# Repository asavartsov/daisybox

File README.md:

# daisybox

Box with daisy seed and IO

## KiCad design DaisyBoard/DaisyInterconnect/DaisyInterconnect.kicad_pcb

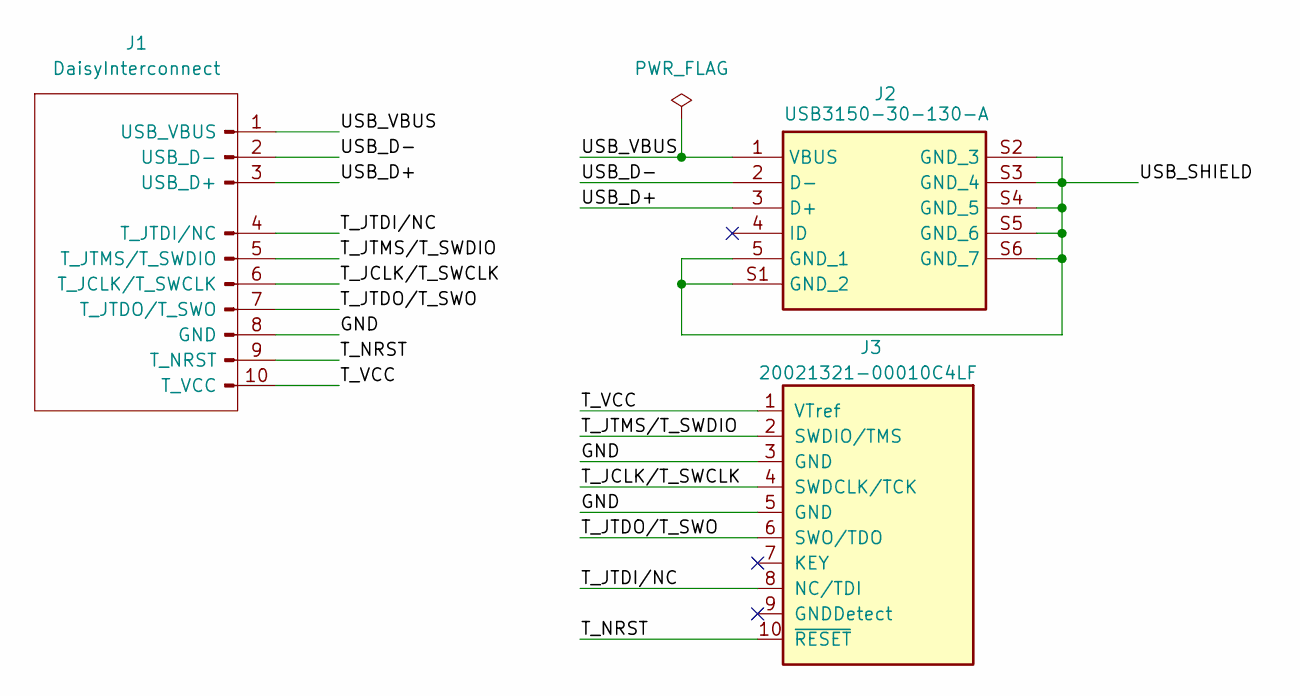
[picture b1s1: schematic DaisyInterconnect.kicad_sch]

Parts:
J1: DaisyInterconnect
J2: USB3150-30-130-A; USB315030130A; Manufacturer_Part_Number USB3150-30-130-A
J3: 20021321-00010C4LF; 2x05_P1.27mm; MPN 20021321-00010C4LF

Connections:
/GND: J1.8 (GND), J3.3 (GND), J3.5 (GND)
/T_JCLK/T_SWCLK: J1.6 (T_JCLK/T_SWCLK), J3.4 (SWDCLK/TCK)
/T_JTDI/NC: J1.4 (T_JTDI/NC), J3.8 (NC/TDI)
/T_JTDO/T_SWO: J1.7 (T_JTDO/T_SWO), J3.6 (SWO/TDO)
/T_JTMS/T_SWDIO: J1.5 (T_JTMS/T_SWDIO), J3.2 (SWDIO/TMS)
/T_NRST: J1.9 (T_NRST), J3.10 (~RESET)
/T_VCC: J1.10 (T_VCC), J3.1 (VTref)
/USB_D+: J1.3 (USB_D+), J2.3 (D+)
/USB_D-: J1.2 (USB_D-), J2.2 (D-)
/USB_SHIELD: J2.5 (GND_1), J2.S1 (GND_2), J2.S2 (GND_3), J2.S3 (GND_4), J2.S4 (GND_5), J2.S5 (GND_6), J2.S6 (GND_7)
/USB_VBUS: J1.1 (USB_VBUS), J2.1 (VBUS)

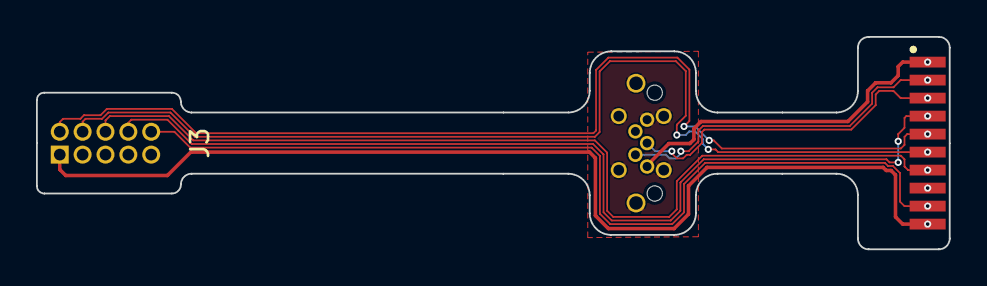
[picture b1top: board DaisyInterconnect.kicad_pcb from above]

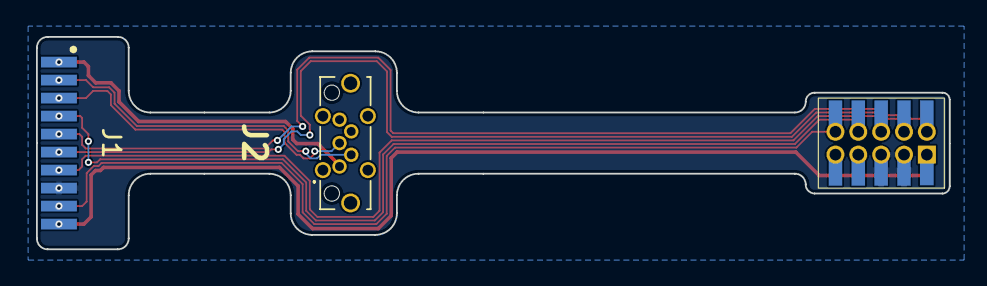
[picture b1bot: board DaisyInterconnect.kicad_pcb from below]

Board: 2 copper layers, 50.7 x 11.8 mm, 3 parts (2 on the bottom side), 11 nets.

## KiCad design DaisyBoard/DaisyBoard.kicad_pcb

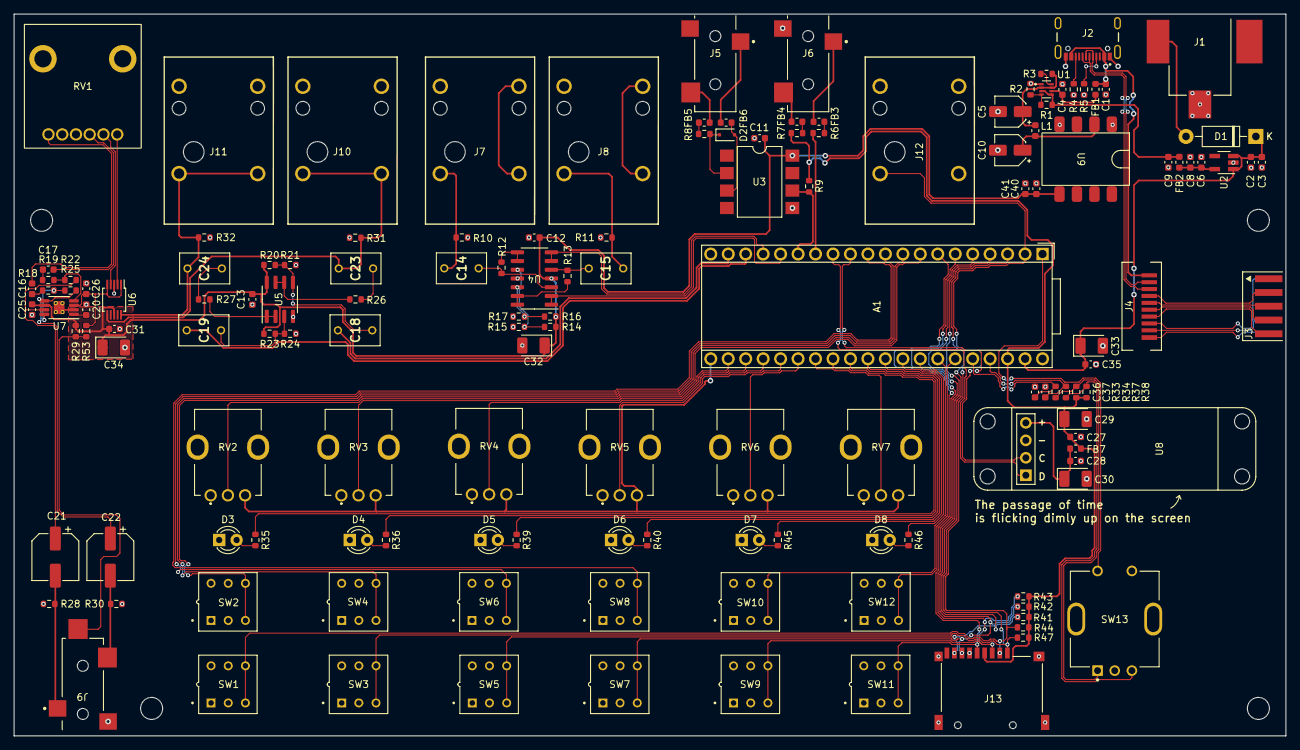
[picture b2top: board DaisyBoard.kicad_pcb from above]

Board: 2 copper layers, 185.0 x 105.0 mm, 149 parts (0 on the bottom side), 111 nets.

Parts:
A1: Electrosmith_Daisy_Seed_Rev4; Electrosmith_Daisy_Seed
C1, C3, C8, C27, C35, C36, C37: 10n; C_0603_1608Metric
C2, C4, C6, C9, C40, C41: 4.7uF; C_0603_1608Metric
C5, C10: 4.7uF; CP_Elec_4x5.4
C11, C12, C13, C20, C25, C26, C28, C31: 100n; C_0603_1608Metric
C14, C15, C18, C19, C23, C24: 1uF; B32529C0105J189
C16, C17: 470n; C_0603_1608Metric
C21, C22: 220uF; CP_Elec_6.3x5.7
C29, C30, C32, C33, C34: 10uF; CP_EIA-3528-15_AVX-H_Pad1.50x2.35mm_HandSolder
D1: 1N5817-T; D_DO-41_SOD81_P10.16mm_Horizontal
D2: 1N4148WS; D_SOD-323F
D3, D4, D5, D6, D7, D8: White; QBL7IW60D-NW
FB1, FB2, FB7: 33 Ohm @ 100 MHz; L_0603_1608Metric
FB3, FB4, FB5, FB6: 1 kOhm @ 100 MHz; L_0603_1608Metric
H1, H2, H3, H4: MountingHole; MountingHole_3.2mm_M3
J1: RASM722X-ND; RASM722X
J2: USB4105-GF-A-120; GCT_USB4105GFA
J3: SWD/JTAG BTB; 009159010061916
J4: DaisyInterconnect
J5, J6: 35RASMT2BHNTRX
J7, J8, J10, J11, J12: ACJM-HHOP
J9: 35RASMT3BHNTRX
J13: 112J-TDAR-R01
L1: 6.8uH; L_0603_1608Metric
R1: 16k; R_0603_1608Metric
R2, R4, R5, R33, R34: 5k1; R_0603_1608Metric
R3, R28, R30, R37, R38: 10k; R_0603_1608Metric
R6: 10R; R_0603_1608Metric
R7: 33R; R_0603_1608Metric
R8: 220R; R_0603_1608Metric
R9: 270R; R_0603_1608Metric
R10, R11, R12, R13, R20, R21, R23, R24, R31, R32: 2M; R_0603_1608Metric
R14, R15, R16, R17: 100k; R_0603_1608Metric
R18, R19: 22k; R_0603_1608Metric
R22, R25, R53: 33k; R_0603_1608Metric
R26, R27: 100R; R_0603_1608Metric
R29: 200k; R_0603_1608Metric
R35, R36, R39, R40, R45, R46: 1k; R_0603_1608Metric
R41, R42, R43, R44, R47: 47k; R_0603_1608Metric
RV1: A50K; PTV112-4420A-A503
RV2, RV3, RV4, RV5, RV6, RV7: B10K; PTV09A-4025F-B103
SW1, SW3, SW5, SW7, SW9, SW11: TL2201OAZA; SW_TL2201EEZA
SW2, SW4, SW6, SW8, SW10, SW12: TL2201EEZA; SW_TL2201EEZA
SW13: PEC11H-4120F-S0020
U1: TPS2116DRLR; SOTFL50P160X60-8N
U2: LDK320AM50R; SOT-23-5_HandSoldering
U3: 6N138S; SMDIP-8_W9.53mm
U4: MCP6004T-I/SL; SOIC-14_3.9x8.7mm_P1.27mm
U5: MCP6002T-I/SN; SOIC-8_3.9x4.9mm_P1.27mm
U6: RS2102XN; MSOP-10_3x3mm_P0.5mm
U7: TPA6110A2DGN
U8: DFR0647
U9: IFS0105S05

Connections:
+3.3V: A1.38 (3V3_D), C27.1, C29.1, FB7.1, J13.4 (VDD), R7.2, R9.1, R37.1, R38.1, R41.1, R42.1, R43.1, R44.1, R47.1
+3.3VA: A1.21 (3V3_A), RV2.3, RV3.3, RV4.3, RV5.3, RV6.3, RV7.3
+3.3V_OLED: C28.1, C30.1, FB7.2, U8.4 (VCC)
+5V: C11.1, C12.1, C13.1, C25.1, C31.1, C32.1, C34.1, C40.1, C41.1, R14.1, R16.1, R20.1, R23.1, R29.1, U3.8 (VCC), U4.4 (V+), U5.8 (V+), U6.8 (VDD), U7.6 (VDD), U9.5 (+Vout)
+5V_DC: C9.1, FB2.2, R1.2, U1.3 (VIN1), U1.5 (MODE)
+5V_USB: C4.1, FB1.2, U1.6 (VIN2)
+9V: A1.39 (VIN), C2.1, C3.1, C33.1, C35.1, D1.1 (K), U2.1 (IN), U2.3 (EN)
/AnalogIO/HP_OUT_L: C21.2, J9.T, R28.1
/AnalogIO/HP_OUT_R: C22.2, J9.R, R30.1
/AnalogIO/L_IN_BIAS: R12.1, U4.8, U4.9 (-)
/AnalogIO/R_IN_BIAS: R13.1, U4.13 (-), U4.14
/DigitalIO/MIDI_IN_D1: FB5.1, J5.R
/DigitalIO/MIDI_IN_D2: FB6.1, J5.T
/DigitalIO/MIDI_OUT_D1: FB3.1, J6.T
/DigitalIO/MIDI_OUT_D2: FB4.1, J6.R
/Power/+5VMUX_LC_OUT: C10.1, L1.2, U9.2 (+Vin)
/Power/+5VMUX_OUT: C5.1, L1.1, R3.2, U1.2 (VOUT), U1.7 (VOUT)
/Power/+5V_DC_LDO: C6.1, C8.1, FB2.1, U2.5 (OUT)
/Power/+9V_DC_IN: D1.2 (A), J1.SLEEVE
AUDIO_L_IN: A1.16 (AUDIO_IN_1), U4.1, U4.2 (-)
AUDIO_L_OUT: A1.18 (AUDIO_OUT_1), C19.1
AUDIO_R_IN: A1.17 (AUDIO_IN_2), U4.6 (-), U4.7
AUDIO_R_OUT: A1.19 (AUDIO_OUT_2), C18.1
ENC_A: A1.36 (USB_D_-), C36.1, R33.2
ENC_B: A1.37 (USB_D_+), C37.1, R34.2
ENC_CLICK: A1.1 (USB_ID), SW13.S1
GND: A1.20 (AGND), A1.40 (DGND), C1.2, C2.2, C3.2, C4.2, C5.2, C6.2, C8.2, C9.2, C10.2, C11.2, C12.2, C13.2, C20.2, C25.2, C26.1, C27.2, C28.2, C29.2, C30.2, C31.2, C32.2, C33.2, C34.2, C35.2, C36.2, C37.2, C40.2, C41.2, D3.1 (K), D4.1 (K), D5.1 (K), D6.1 (K), D7.1 (K), D8.1 (K), J1.TIP, J2.A1_B12 (GND), J2.B1_A12 (GND), J6.S, J7.S, J8.S, J9.S, J10.S, J10.SN, J11.S, J11.SN, J12.S, J13.6 (VSS), J13.10 (SHIELD), R2.1, R4.1, R5.1, R10.2, R11.2, R15.2, R17.2, R21.2, R24.2, R28.2, R30.2, R31.2, R32.2, RV1.1, RV1.1*, RV2.1, RV3.1, RV4.1, RV5.1, RV6.1, RV7.1, SW1.2 (B), SW1.5 (B), SW2.2 (B), SW2.5 (B), SW3.2 (B), SW3.5 (B), SW4.2 (B), SW4.5 (B), SW5.2 (B), SW5.5 (B), SW6.2 (B), SW6.5 (B), SW7.2 (B), SW7.5 (B), SW8.2 (B), SW8.5 (B), SW9.2 (B), SW9.5 (B), SW10.2 (B), SW10.5 (B), SW11.2 (B), SW11.5 (B), SW12.2 (B), SW12.5 (B), SW13.C, SW13.S2, U1.1 (GND), U2.2 (GND), U3.5 (GND), U4.11 (V-), U5.4 (V-), U6.3 (GND), U7.2 (GND), U7.9 (GND), U8.3 (GND), U9.1 (-Vin), U9.4 (-Vout)
HP_DETECT: C26.2, R53.1, U6.1 (IN1), U6.5 (IN2), U7.3 (SHDN)
HP_VOL_L: RV1.3, U6.2 (S1B)
HP_VOL_R: RV1.3*, U6.4 (S2B)
LED_1: A1.28 (ADC_6), R35.2
LED_2: A1.29 (DAC_OUT2), R36.2
LED_3: A1.30 (DAC_OUT1), R39.2
LED_4: A1.31 (SAI2_MCLK), R40.2
LED_5: A1.32 (SAI2_SD_B), R45.2
LED_6: A1.33 (SAI2_SD_A), R46.2
MAIN_IN_L: C14.1, J7.T, R10.1
MAIN_IN_R: C15.1, J8.T, R11.1
MAIN_OUT_L: C24.2, J11.T, J11.TN, R32.1, U6.10 (D1)
MAIN_OUT_R: C23.2, J10.T, J10.TN, R31.1, U6.6 (D2)
MIDI_IN: A1.15 (USART1_RX), R9.2, U3.6 (VO2)
MIDI_OUT: A1.14 (USART1_TX), R6.2
unnamed: C16.1, RV1.2
unnamed: C16.2, R18.2
unnamed: C17.1, RV1.2*
unnamed: C17.2, R19.2
unnamed: C23.1, R26.2
unnamed: C24.1, R27.2
unnamed: D2.2 (A), FB6.2, U3.3 (C2)
unnamed: D2.1 (K), R8.2, U3.2 (C1)
unnamed: D3.2 (A), R35.1
unnamed: D4.2 (A), R36.1
unnamed: D5.2 (A), R39.1
unnamed: D6.2 (A), R40.1
unnamed: D7.2 (A), R45.1
unnamed: D8.2 (A), R46.1
unnamed: FB3.2, R6.1
unnamed: FB4.2, R7.1
unnamed: FB5.2, R8.1
unnamed: J2.A5 (CC1), R5.2
unnamed: J2.B5 (CC2), R4.2
unnamed: J3.6 (GND), J4.8 (GND)
unnamed: J3.4 (T_JCLK/T_SWCLK), J4.6 (T_JCLK/T_SWCLK)
unnamed: J3.2 (T_JTDI/NC), J4.4 (T_JTDI/NC)
unnamed: J3.5 (T_JTDO/T_SWO), J4.7 (T_JTDO/T_SWO)
unnamed: J3.3 (T_JTMS/T_SWDIO), J4.5 (T_JTMS/T_SWDIO)
unnamed: J3.9 (T_NRST), J4.9 (T_NRST)
unnamed: J3.10 (T_VCC), J4.10 (T_VCC)
unnamed: J7.SN, J7.TN
unnamed: J8.SN, J8.TN
unnamed: J9.TN, R29.2, R53.2
unnamed: R33.1, R37.2, SW13.A
unnamed: R34.1, R38.2, SW13.B
unnamed: R1.1, R2.2, U1.4 (PR1)
unnamed: R3.1, U1.8 (ST)
unnamed: C14.2, R12.2, U4.3 (+)
unnamed: C15.2, R13.2, U4.5 (+)
unnamed: R14.2, R15.1, U4.10 (+)
unnamed: R16.2, R17.1, U4.12 (+)
unnamed: C19.2, R23.2, R24.1, U5.3 (+)
unnamed: R27.1, U5.1, U5.2 (-)
unnamed: C18.2, R20.2, R21.1, U5.5 (+)
unnamed: R26.1, U5.6 (-), U5.7
unnamed: C20.1, U7.1 (BYPASS)
unnamed: R18.1, R25.2, U7.8 (IN1-)
unnamed: R19.1, R22.2, U7.4 (IN2-)
unnamed: C21.1, R22.1, U7.7 (VO1)
unnamed: C22.1, R25.1, U7.5 (VO2)
OLED_SCL: A1.12 (I2C1_SCL), U8.2 (SCL)
OLED_SDA: A1.13 (I2C1_SDA), U8.1 (SDA)
POT_1: A1.22 (ADC_0), RV2.2
POT_2: A1.23 (ADC_1), RV3.2
POT_3: A1.24 (ADC_2), RV4.2
POT_4: A1.25 (ADC_3), RV5.2
POT_5: A1.26 (ADC_4), RV6.2
POT_6: A1.27 (ADC_5), RV7.2
PUSH_1: A1.2 (SD_DATA_3), J12.T, J13.2 (DAT3/CD), R44.2, SW1.3 (C), SW1.6 (C)
PUSH_2: A1.3 (SD_DATA_2), J13.1 (DAT2), R47.2, SW3.3 (C), SW3.6 (C)
PUSH_3: A1.4 (SD_DATA_1), J13.8 (DAT1), R41.2, SW5.3 (C), SW5.6 (C)
PUSH_4: A1.5 (SD_DATA_0), J13.7 (DAT0), R42.2, SW7.3 (C), SW7.6 (C)
PUSH_5: A1.6 (SD_CMD), J13.3 (CMD), R43.2, SW9.3 (C), SW9.6 (C)
PUSH_6: A1.7 (SD_CLK), J13.5 (CLK), SW11.3 (C), SW11.6 (C)
SW_1: A1.8 (SPI1_CS), SW2.3 (C), SW2.6 (C)
SW_2: A1.9 (SPI1_SCK), SW4.3 (C), SW4.6 (C)
SW_3: A1.10 (SPI1_POCI), SW6.3 (C), SW6.6 (C)
SW_4: A1.11 (SPI1_PICO), SW8.3 (C), SW8.6 (C)
SW_5: A1.34 (SAI2_FS), SW10.3 (C), SW10.6 (C)
SW_6: A1.35 (SAI2_SCK), SW12.3 (C), SW12.6 (C)
USB_D+: J2.A6 (D+), J2.B6 (D+), J4.3 (USB_D+)
USB_D-: J2.A7 (D-), J2.B7 (D-), J4.2 (USB_D-)
USB_VBUS: C1.1, FB1.1, J2.A4_B9 (VBUS), J2.B4_A9 (VBUS), J4.1 (USB_VBUS)

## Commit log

2023-12-05 Add schematic
